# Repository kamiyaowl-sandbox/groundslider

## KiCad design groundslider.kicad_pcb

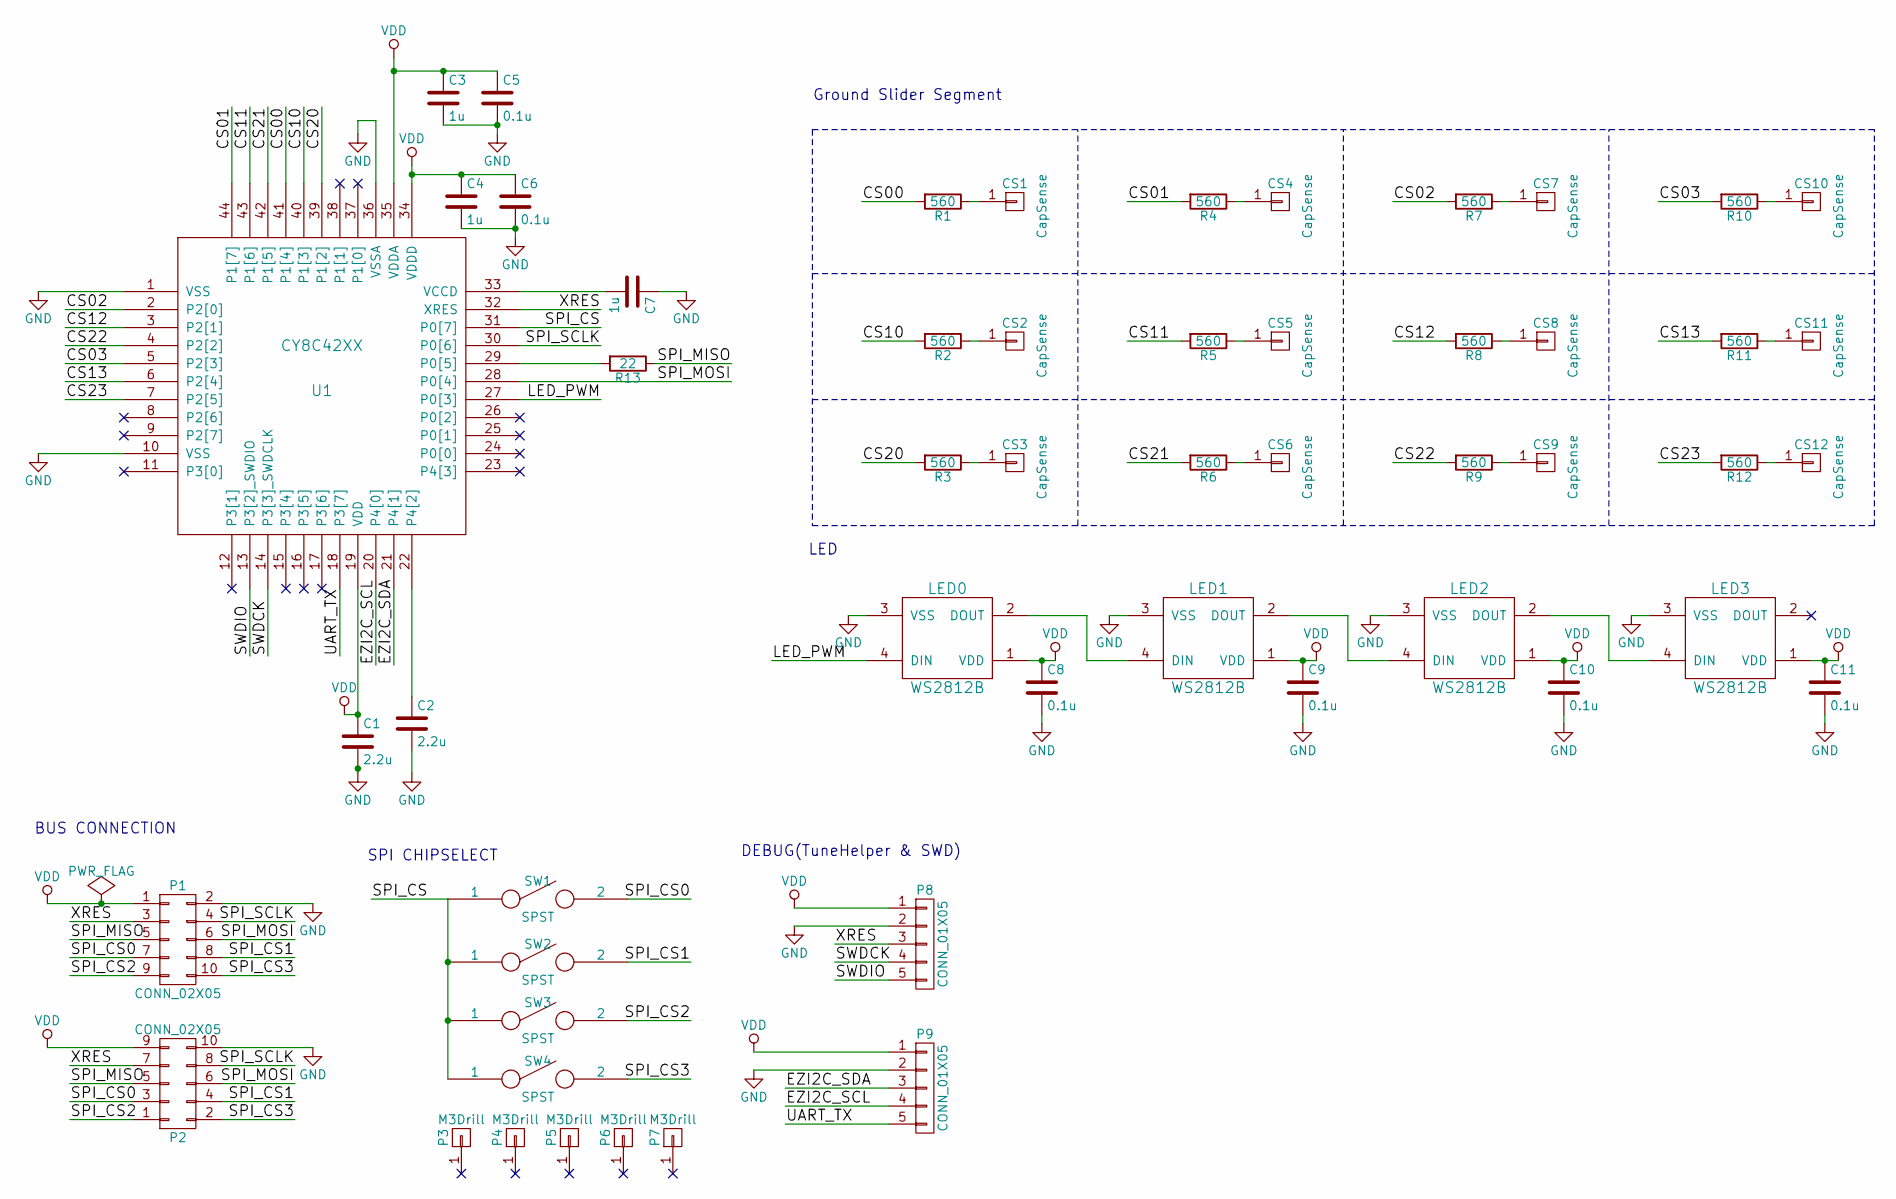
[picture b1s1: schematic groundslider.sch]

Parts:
C1, C2: 2.2u; HANDSOL_0603
C3, C4, C7: 1u; HANDSOL_0603
C5, C6, C8, C9, C10, C11: 0.1u; HANDSOL_0603
CS1, CS2, CS3, CS4, CS5, CS6, CS7, CS8, CS9, CS10, CS11, CS12: CapSense; CapSense_BTN
LED0, LED1, LED2, LED3: WS2812B
P1, P2: CONN_02X05; Pin_Header_Angled_2x05
P3, P4, P5, P6, P7: M3Drill; M3Drill2
P8, P9: CONN_01X05; Pin_Header_Straight_1x05
R1, R2, R3, R4, R5, R6, R7, R8, R9, R10, R11, R12: 560; HANDSOL_0603
R13: 22; HANDSOL_0603
SW1, SW2, SW3, SW4: SPST; HANDSOL_0603
U1: CY8C42XX; CY_TQFP44(0.8)

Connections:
/CS00: R1.2, U1.41 (P1[4])
/CS01: R4.2, U1.44 (P1[7])
/CS02: R7.2, U1.2 (P2[0])
/CS03: R10.2, U1.5 (P2[3])
/CS10: R2.2, U1.40 (P1[3])
/CS11: R5.2, U1.43 (P1[6])
/CS12: R8.2, U1.3 (P2[1])
/CS13: R11.2, U1.6 (P2[4])
/CS20: R3.2, U1.39 (P1[2])
/CS21: R6.2, U1.42 (P1[5])
/CS22: R9.2, U1.4 (P2[2])
/CS23: R12.2, U1.7 (P2[5])
/EZI2C_SCL: P9.4, U1.20 (P4[0])
/EZI2C_SDA: P9.3, U1.21 (P4[1])
/LED_PWM: LED0.4 (DIN), U1.27 (P0[3])
/SPI_CS: SW1.1, SW2.1, SW3.1, SW4.1, U1.31 (P0[7])
/SPI_CS0: P1.7, P2.3, SW1.2
/SPI_CS1: P1.8, P2.4, SW2.2
/SPI_CS2: P1.9, P2.1, SW3.2
/SPI_CS3: P1.10, P2.2, SW4.2
/SPI_MISO: P1.5, P2.5, R13.1
/SPI_MOSI: P1.6, P2.6, U1.28 (P0[4])
/SPI_SCLK: P1.4, P2.8, U1.30 (P0[6])
/SWDCK: P8.4, U1.14 (P3[3]_SWDCLK)
/SWDIO: P8.5, U1.13 (P3[2]_SWDIO)
/UART_TX: P9.5, U1.18 (P3[7])
/XRES: P1.3, P2.7, P8.3, U1.32 (XRES)
GND: C1.2, C2.2, C3.2, C4.2, C5.2, C6.2, C7.1, C8.2, C9.2, C10.2, C11.2, LED0.3 (VSS), LED1.3 (VSS), LED2.3 (VSS), LED3.3 (VSS), P1.2, P2.10, P8.2, P9.2, U1.1 (VSS), U1.10 (VSS), U1.36 (VSSA)
unnamed: C2.1, U1.22 (P4[2])
unnamed: C7.2, U1.33 (VCCD)
unnamed: CS1.1, R1.1
unnamed: CS2.1, R2.1
unnamed: CS3.1, R3.1
unnamed: CS4.1, R4.1
unnamed: CS5.1, R5.1
unnamed: CS6.1, R6.1
unnamed: CS7.1, R7.1
unnamed: CS8.1, R8.1
unnamed: CS9.1, R9.1
unnamed: CS10.1, R10.1
unnamed: CS11.1, R11.1
unnamed: CS12.1, R12.1
unnamed: LED0.2 (DOUT), LED1.4 (DIN)
unnamed: LED1.2 (DOUT), LED2.4 (DIN)
unnamed: LED2.2 (DOUT), LED3.4 (DIN)
unnamed: R13.2, U1.29 (P0[5])
VDD: C1.1, C3.1, C4.1, C5.1, C6.1, C8.1, C9.1, C10.1, C11.1, LED0.1 (VDD), LED1.1 (VDD), LED2.1 (VDD), LED3.1 (VDD), P1.1, P2.9, P8.1, P9.1, U1.19 (VDD), U1.34 (VDDD), U1.35 (VDDA)

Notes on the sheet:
BUS CONNECTION
SPI CHIPSELECT
DEBUG(TuneHelper & SWD)
LED
Ground Slider Segment

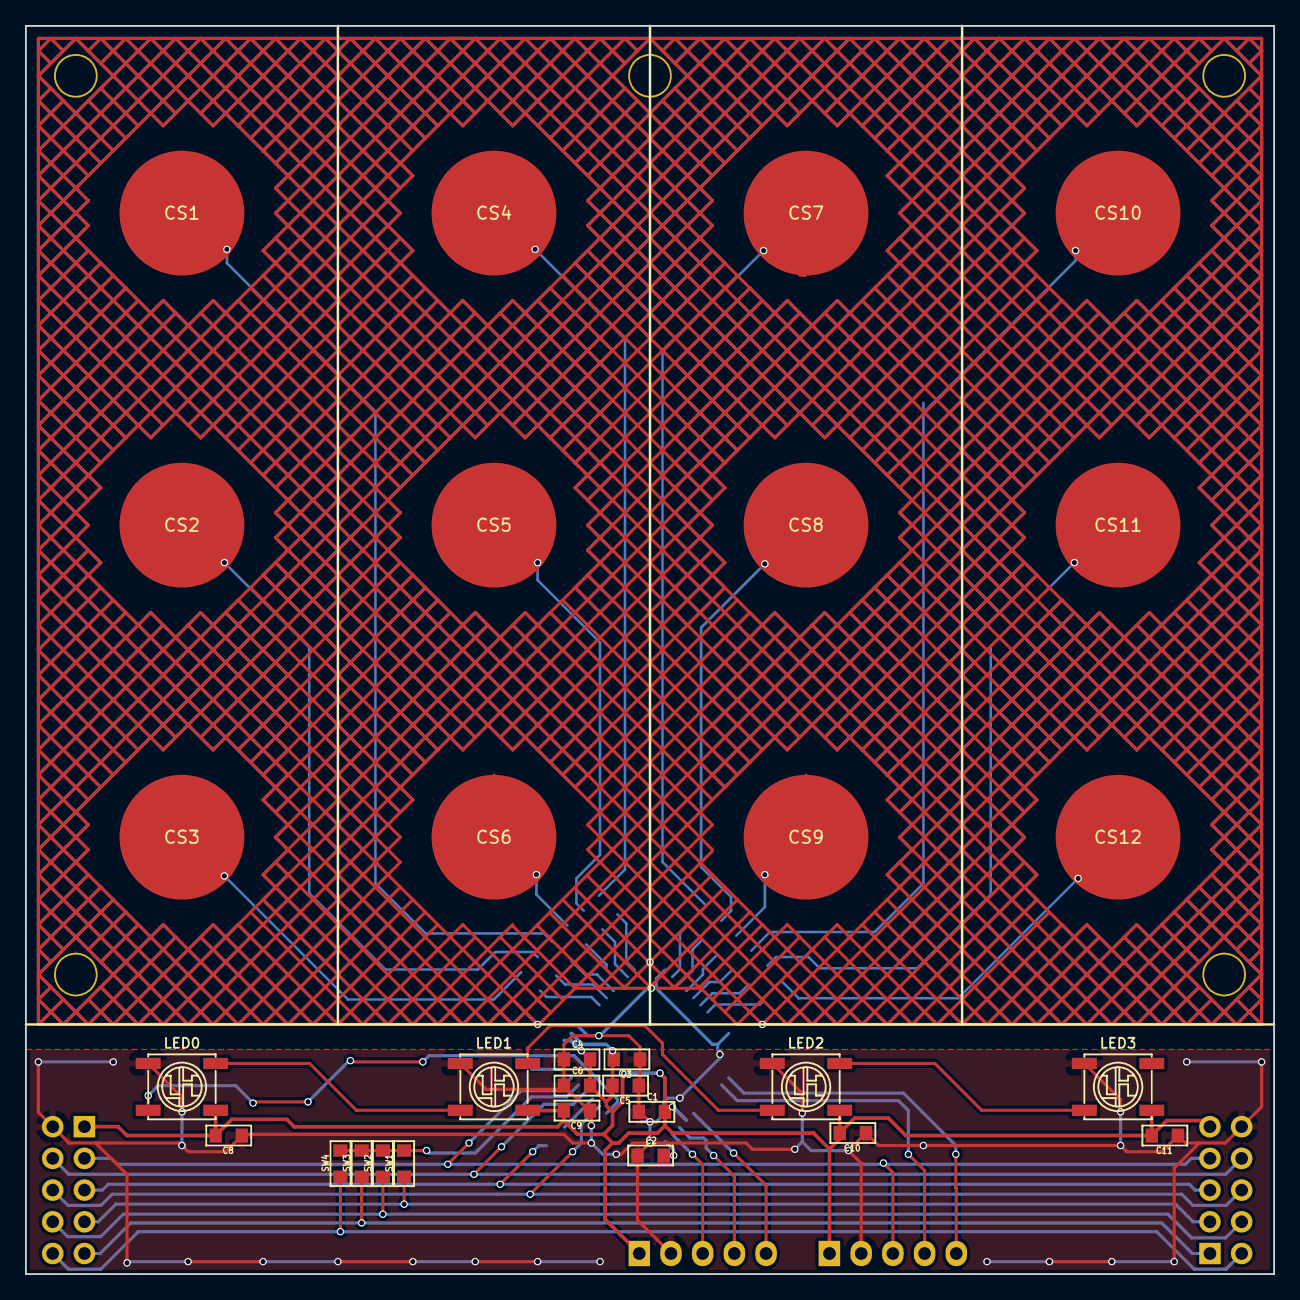
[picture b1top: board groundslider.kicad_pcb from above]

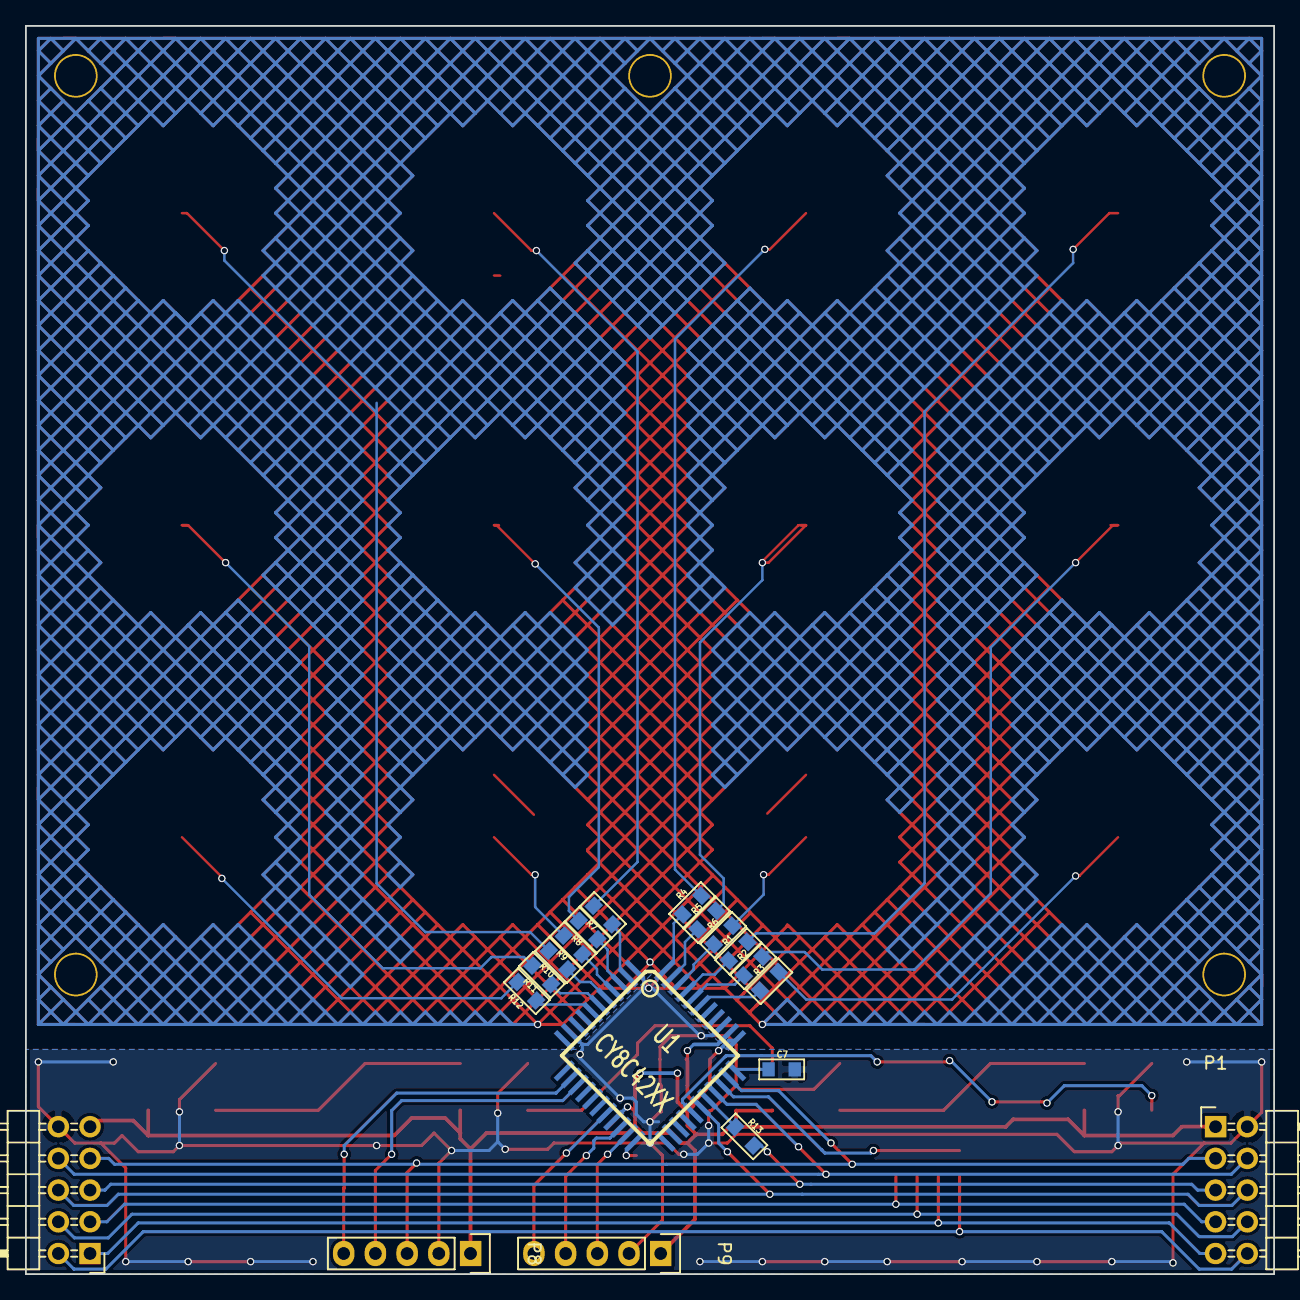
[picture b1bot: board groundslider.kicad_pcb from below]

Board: 2 copper layers, 100.0 x 100.0 mm, 54 parts (19 on the bottom side), 47 nets.

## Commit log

2016-03-27 CapSense配線
2016-03-27 ハッチング前
2016-03-27 表面ハッチング
2016-03-27 裏面ハッチング
